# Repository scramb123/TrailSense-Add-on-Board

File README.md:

# TrailSense-Add-on-Board

Sensorwatch Add-On is an expansion board designed specifically for the Sensorwatch, equipped with both a barometer and a magnetometer. This add-on enhances the Sensorwatch’s capabilities, making it ideal for outdoor enthusiasts who want reliable altitude and directional data while exploring nature. Please note that this add-on is currently in development and has not yet been fully tested.

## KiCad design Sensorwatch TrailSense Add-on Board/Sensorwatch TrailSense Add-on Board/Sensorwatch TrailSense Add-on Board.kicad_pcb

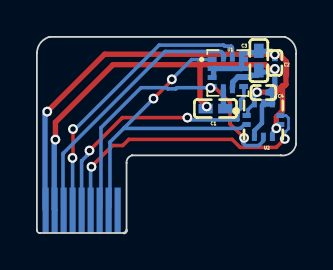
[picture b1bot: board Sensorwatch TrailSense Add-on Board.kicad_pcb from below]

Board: 2 copper layers, 14.4 x 10.9 mm, 7 parts (7 on the bottom side), 9 nets.

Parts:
C1: 220nF; C0402
C2, C4: 100nF; C0201
C3: 10uF; C0402
J1: OSO-SWAB-B1-00 Sensor Watch Accelerometer{colon}FH19C9S05SH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
U1: LSM303AGRTR; LGA-12_L2.0-W2.0-P0.50-BL
U2: LPS22DFTR; HLGA-10_L2.0-W2.0-P0.50-TL

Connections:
$1N377: C1.1, U1.5
A1_INT1: J1.6, U2.7
A2_INT3: J1.5, U1.7
A3_INT2: J1.4, U1.11
A4_INT1: J1.3, U1.12
GND: C1.2, C2.2, C3.2, C4.2, J1.2, U1.6, U1.8, U2.3, U2.8, U2.9
SCL: J1.8, U1.1, U2.2
SDA: J1.7, U1.4, U2.4
VCC: C2.1, C3.1, C4.1, J1.1, U1.2, U1.3, U1.9, U1.10, U2.1, U2.5, U2.6, U2.10
